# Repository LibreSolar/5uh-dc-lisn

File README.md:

# 5uH-DC-LISN
5uH DC LISN (-10 dB attenuation)

This LISN enables you to perform basic EMC testing with your DC devices, e.g. power supplies.

The layout (especially the attenuation) is based on Linear Technology DC2130A board design and a [thread in the EEVblog forum](http://www.eevblog.com/forum/projects/5uh-lisn-for-spectrum-analyzer-emcemi-work/msg404662/#msg404662).

Further information on EMC testing can be found in [Würth Application Note ANP005](http://www.we-online.de/web/en/electronic_components/produkte_pb/application_notes/emv_filter_fuer_dc_dc_schaltregler_optimiert.php).

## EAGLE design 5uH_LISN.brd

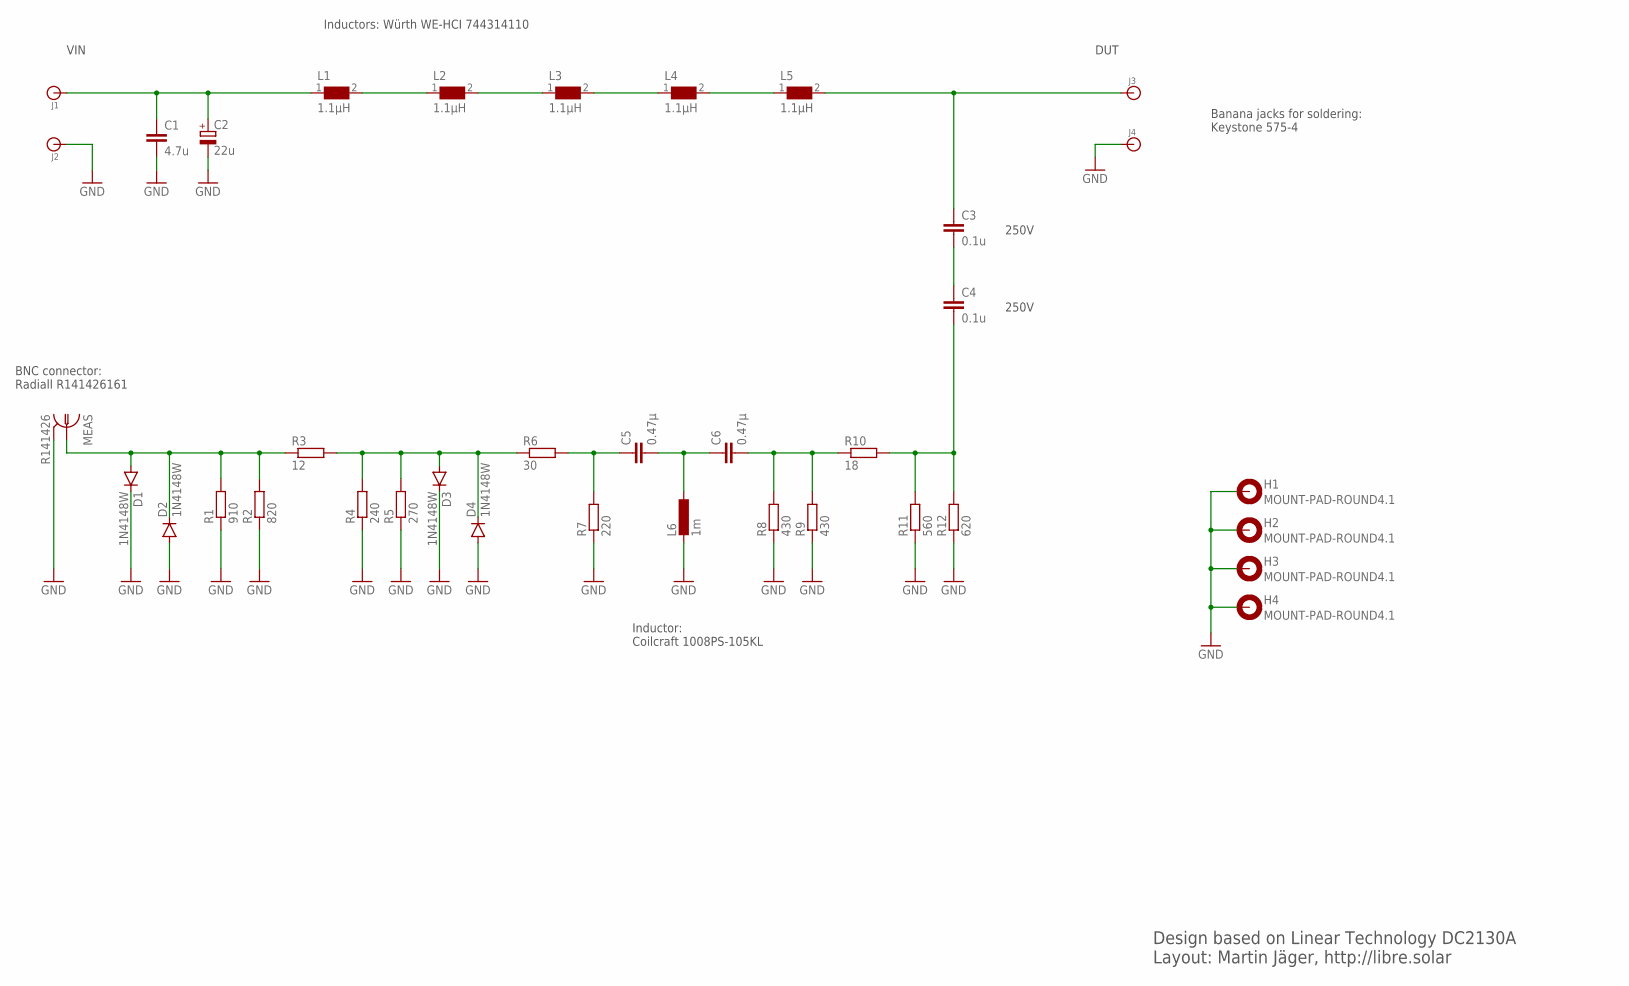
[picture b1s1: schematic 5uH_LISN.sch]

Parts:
C1: 4.7u; C1210
C2: 22u; PANASONIC_B
C3, C4: 0.1u; C1206
C5, C6: 0.47µ; C0805
D1, D2, D3, D4: 1N4148W; SOD-123; MPN 1N4148W-7-F.
H1, H2, H3, H4: MOUNT-PAD-ROUND4.1; 4,1-PAD
J1, J2, J3, J4: BANANA_CONN
L1, L2, L3, L4, L5: 1.1µH; WE-HCI_7030/7040/7050
L6: 1m; COILCRAFT_1008PS
MEAS: R141426
R1: 910; R0805
R2: 820; R0805
R3: 12; R0805
R4: 240; R0805
R5: 270; R0805
R6: 30; R0805
R7: 220; R0805
R8, R9: 430; R0805
R10: 18; R0805
R11: 560; R0805
R12: 620; R0805

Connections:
GND: C1.2, C2.-, D1.C, D2.A, D3.C, D4.A, H1.B4,1, H2.B4,1, H3.B4,1, H4.B4,1, J2.P$1, J4.P$1, L6.P$2 (2), MEAS.2, MEAS.3 (2), MEAS.4 (2), MEAS.5 (2), R1.1, R2.1, R4.1, R5.1, R7.1, R8.1, R9.1, R11.1, R12.1
unnamed: C1.1, C2.+, J1.P$1, L1.1
unnamed: L1.2, L2.1
unnamed: L2.2, L3.1
unnamed: L3.2, L4.1
unnamed: L4.2, L5.1
unnamed: C3.1, J3.P$1, L5.2
unnamed: C3.2, C4.1
unnamed: D1.A, D2.C, MEAS.1, R1.2, R2.2, R3.1
unnamed: D3.A, D4.C, R3.2, R4.2, R5.2, R6.1
unnamed: C5.1, R6.2, R7.2
unnamed: C5.2, C6.1, L6.P$1 (1)
unnamed: C6.2, R8.2, R9.2, R10.1
unnamed: C4.2, R10.2, R11.2, R12.2

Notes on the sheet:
Inductors: Würth WE-HCI 744314110
Banana jacks for soldering: Keystone 575-4
BNC connector: Radiall R141426161
Inductor: Coilcraft 1008PS-105KL
VIN
DUT
250V
Design based on Linear Technology DC2130A Layout: Martin Jäger, http://libre.solar

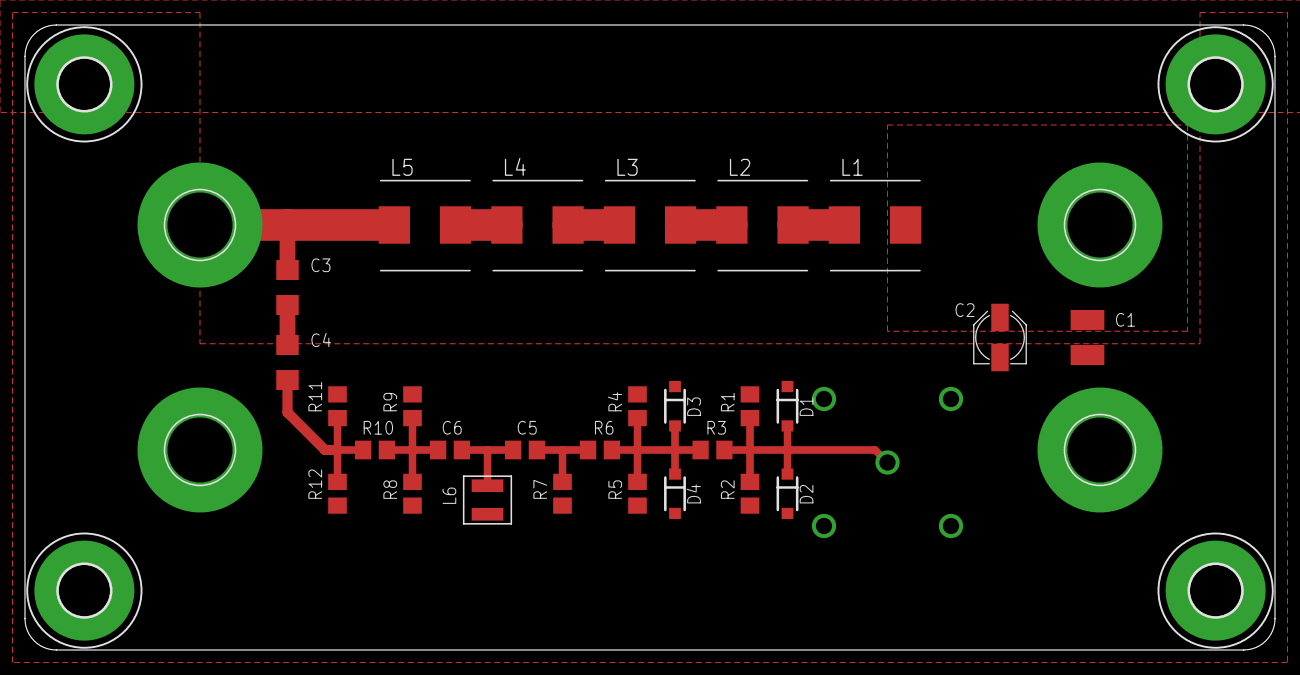
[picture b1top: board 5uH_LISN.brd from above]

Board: 2 copper layers, 100.0 x 50.0 mm, 37 parts (1 on the bottom side), 14 nets.

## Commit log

2016-10-04 Initial commit of schematic and board
2019-04-22 Imported to kicad.
2019-04-22 Cleaned-up kicad layout.
2019-04-22 Renamed folder containing kicad files.
2019-04-23 Replaced C2 with C2220 for higher voltage rating. Schematic symbol for C2 no longer polarized. More via stitching.

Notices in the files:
parts and their libraries:
PowerMagnetics: Copyright: Würth Elektronik
SparkFun-DiscreteSemi: Licensing: Creative Commons ShareAlike 4.0 International - https://creativecommons.org/licenses/by-sa/4.0
